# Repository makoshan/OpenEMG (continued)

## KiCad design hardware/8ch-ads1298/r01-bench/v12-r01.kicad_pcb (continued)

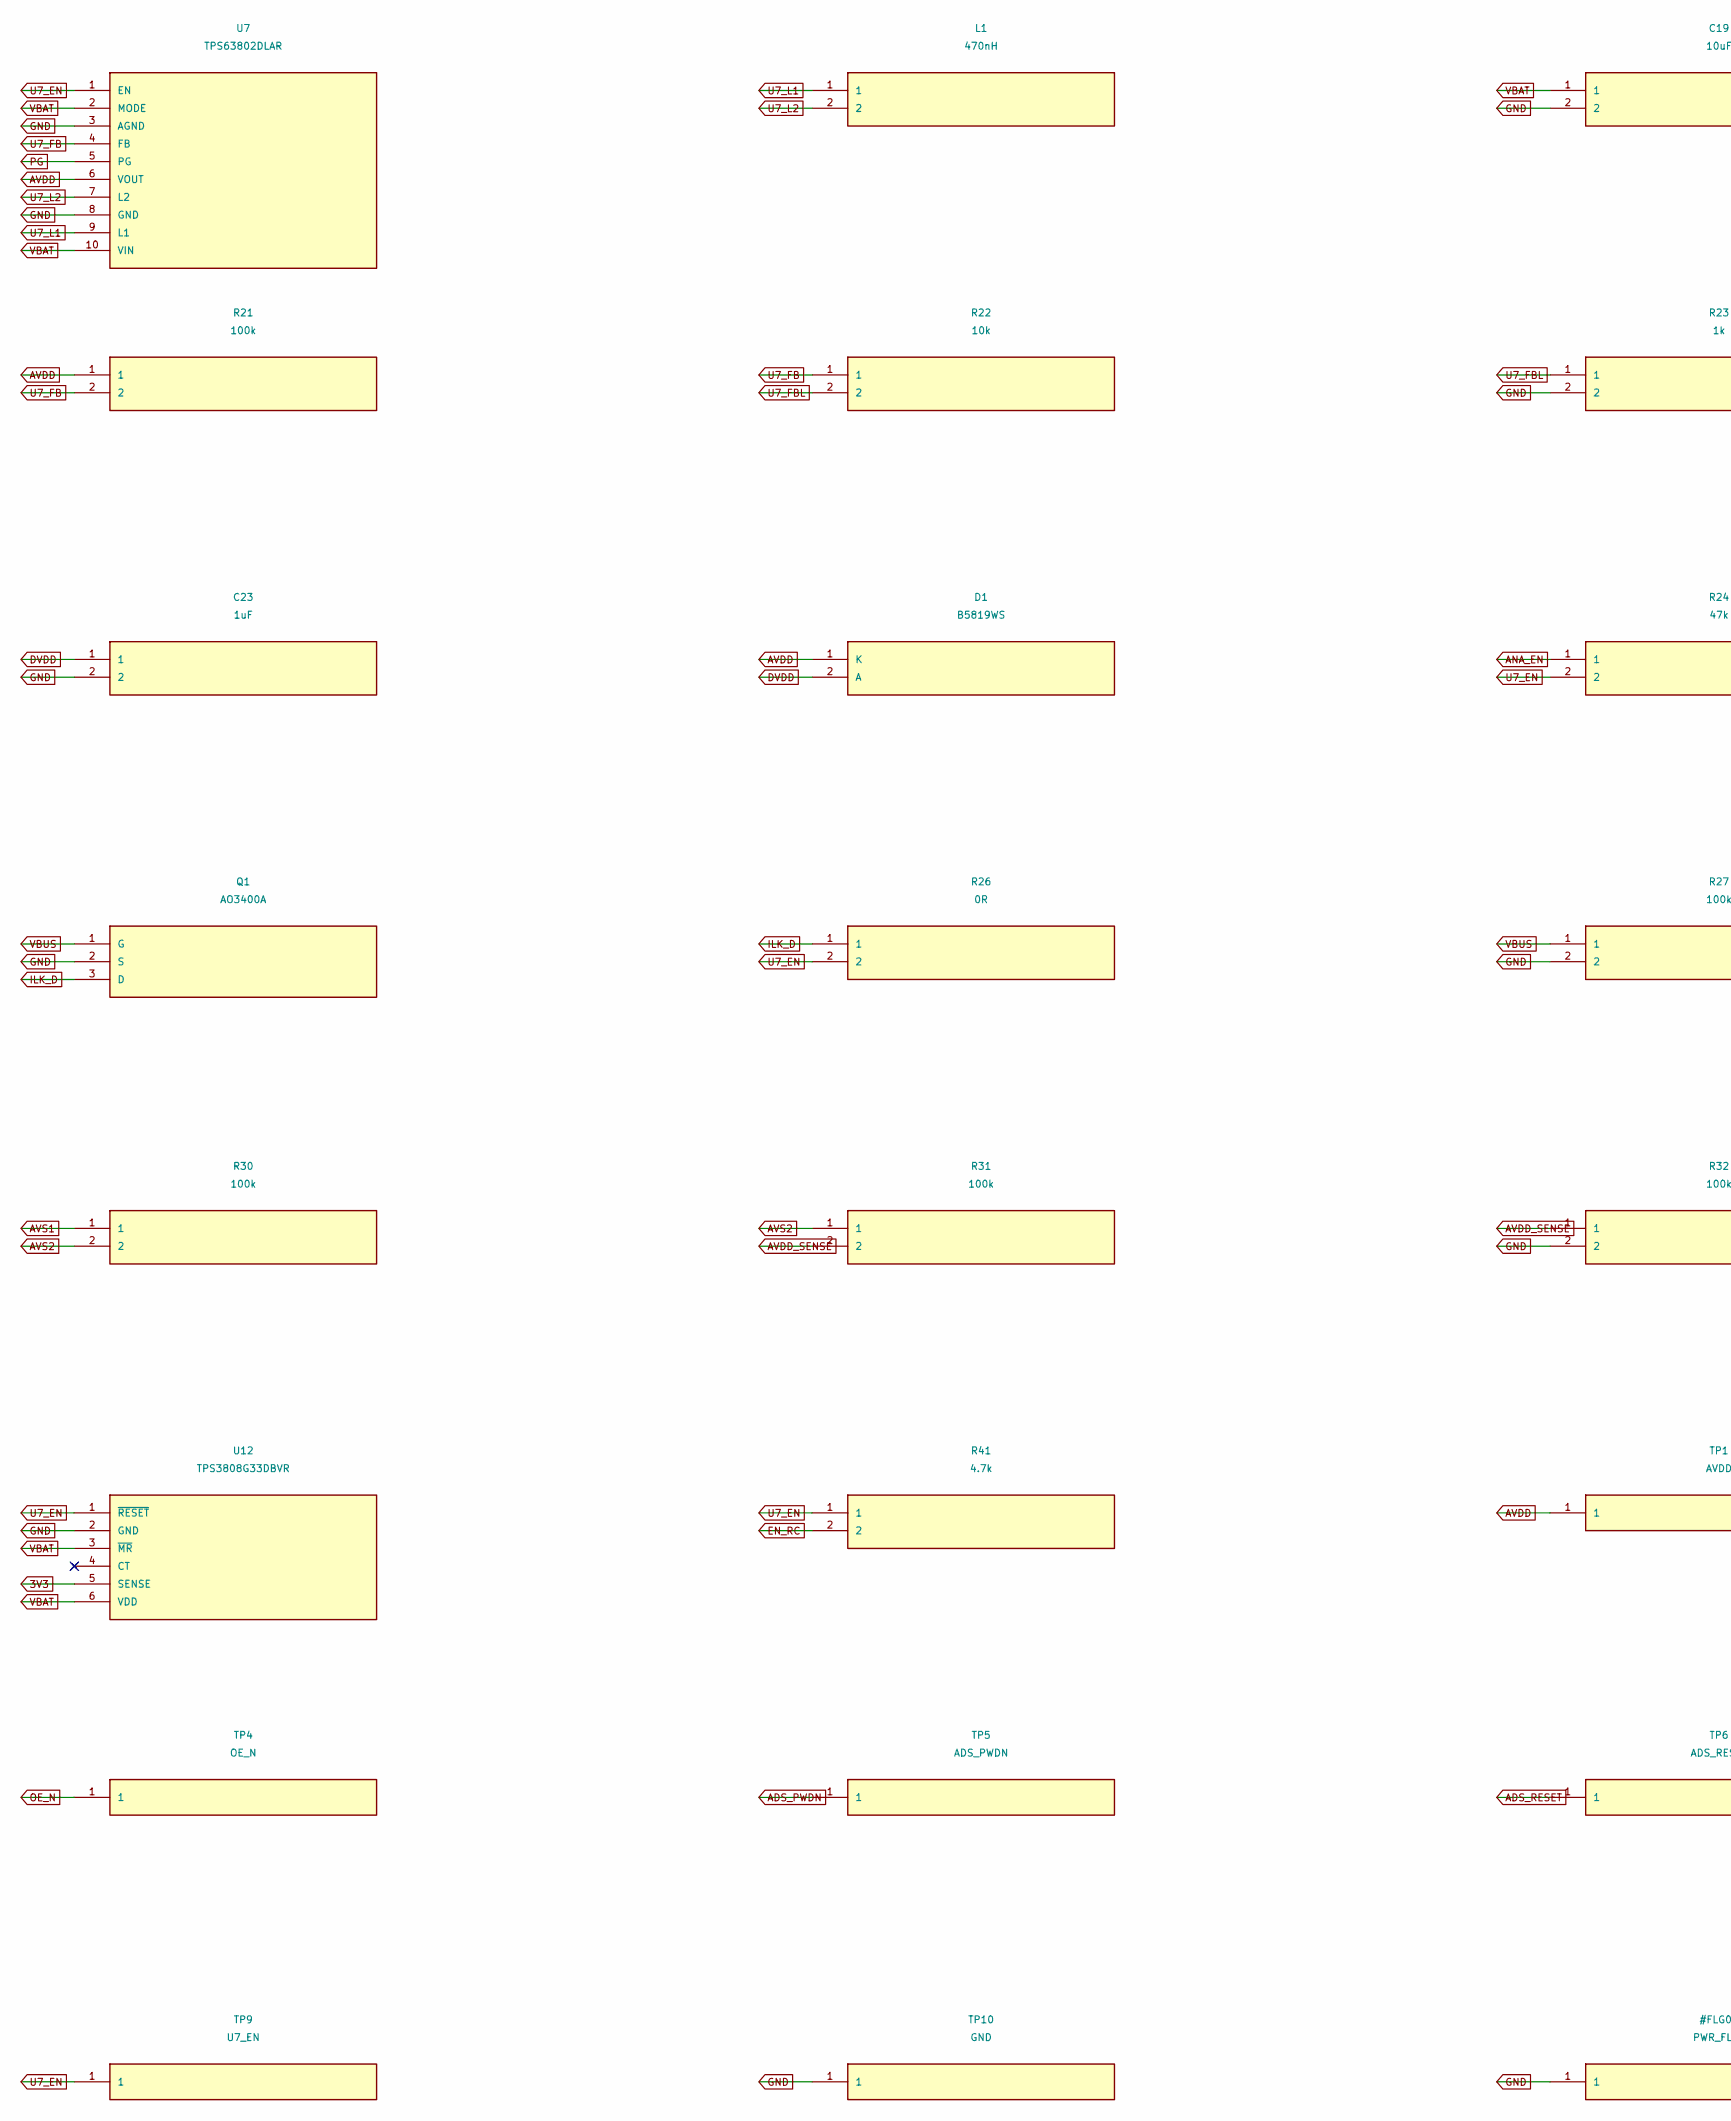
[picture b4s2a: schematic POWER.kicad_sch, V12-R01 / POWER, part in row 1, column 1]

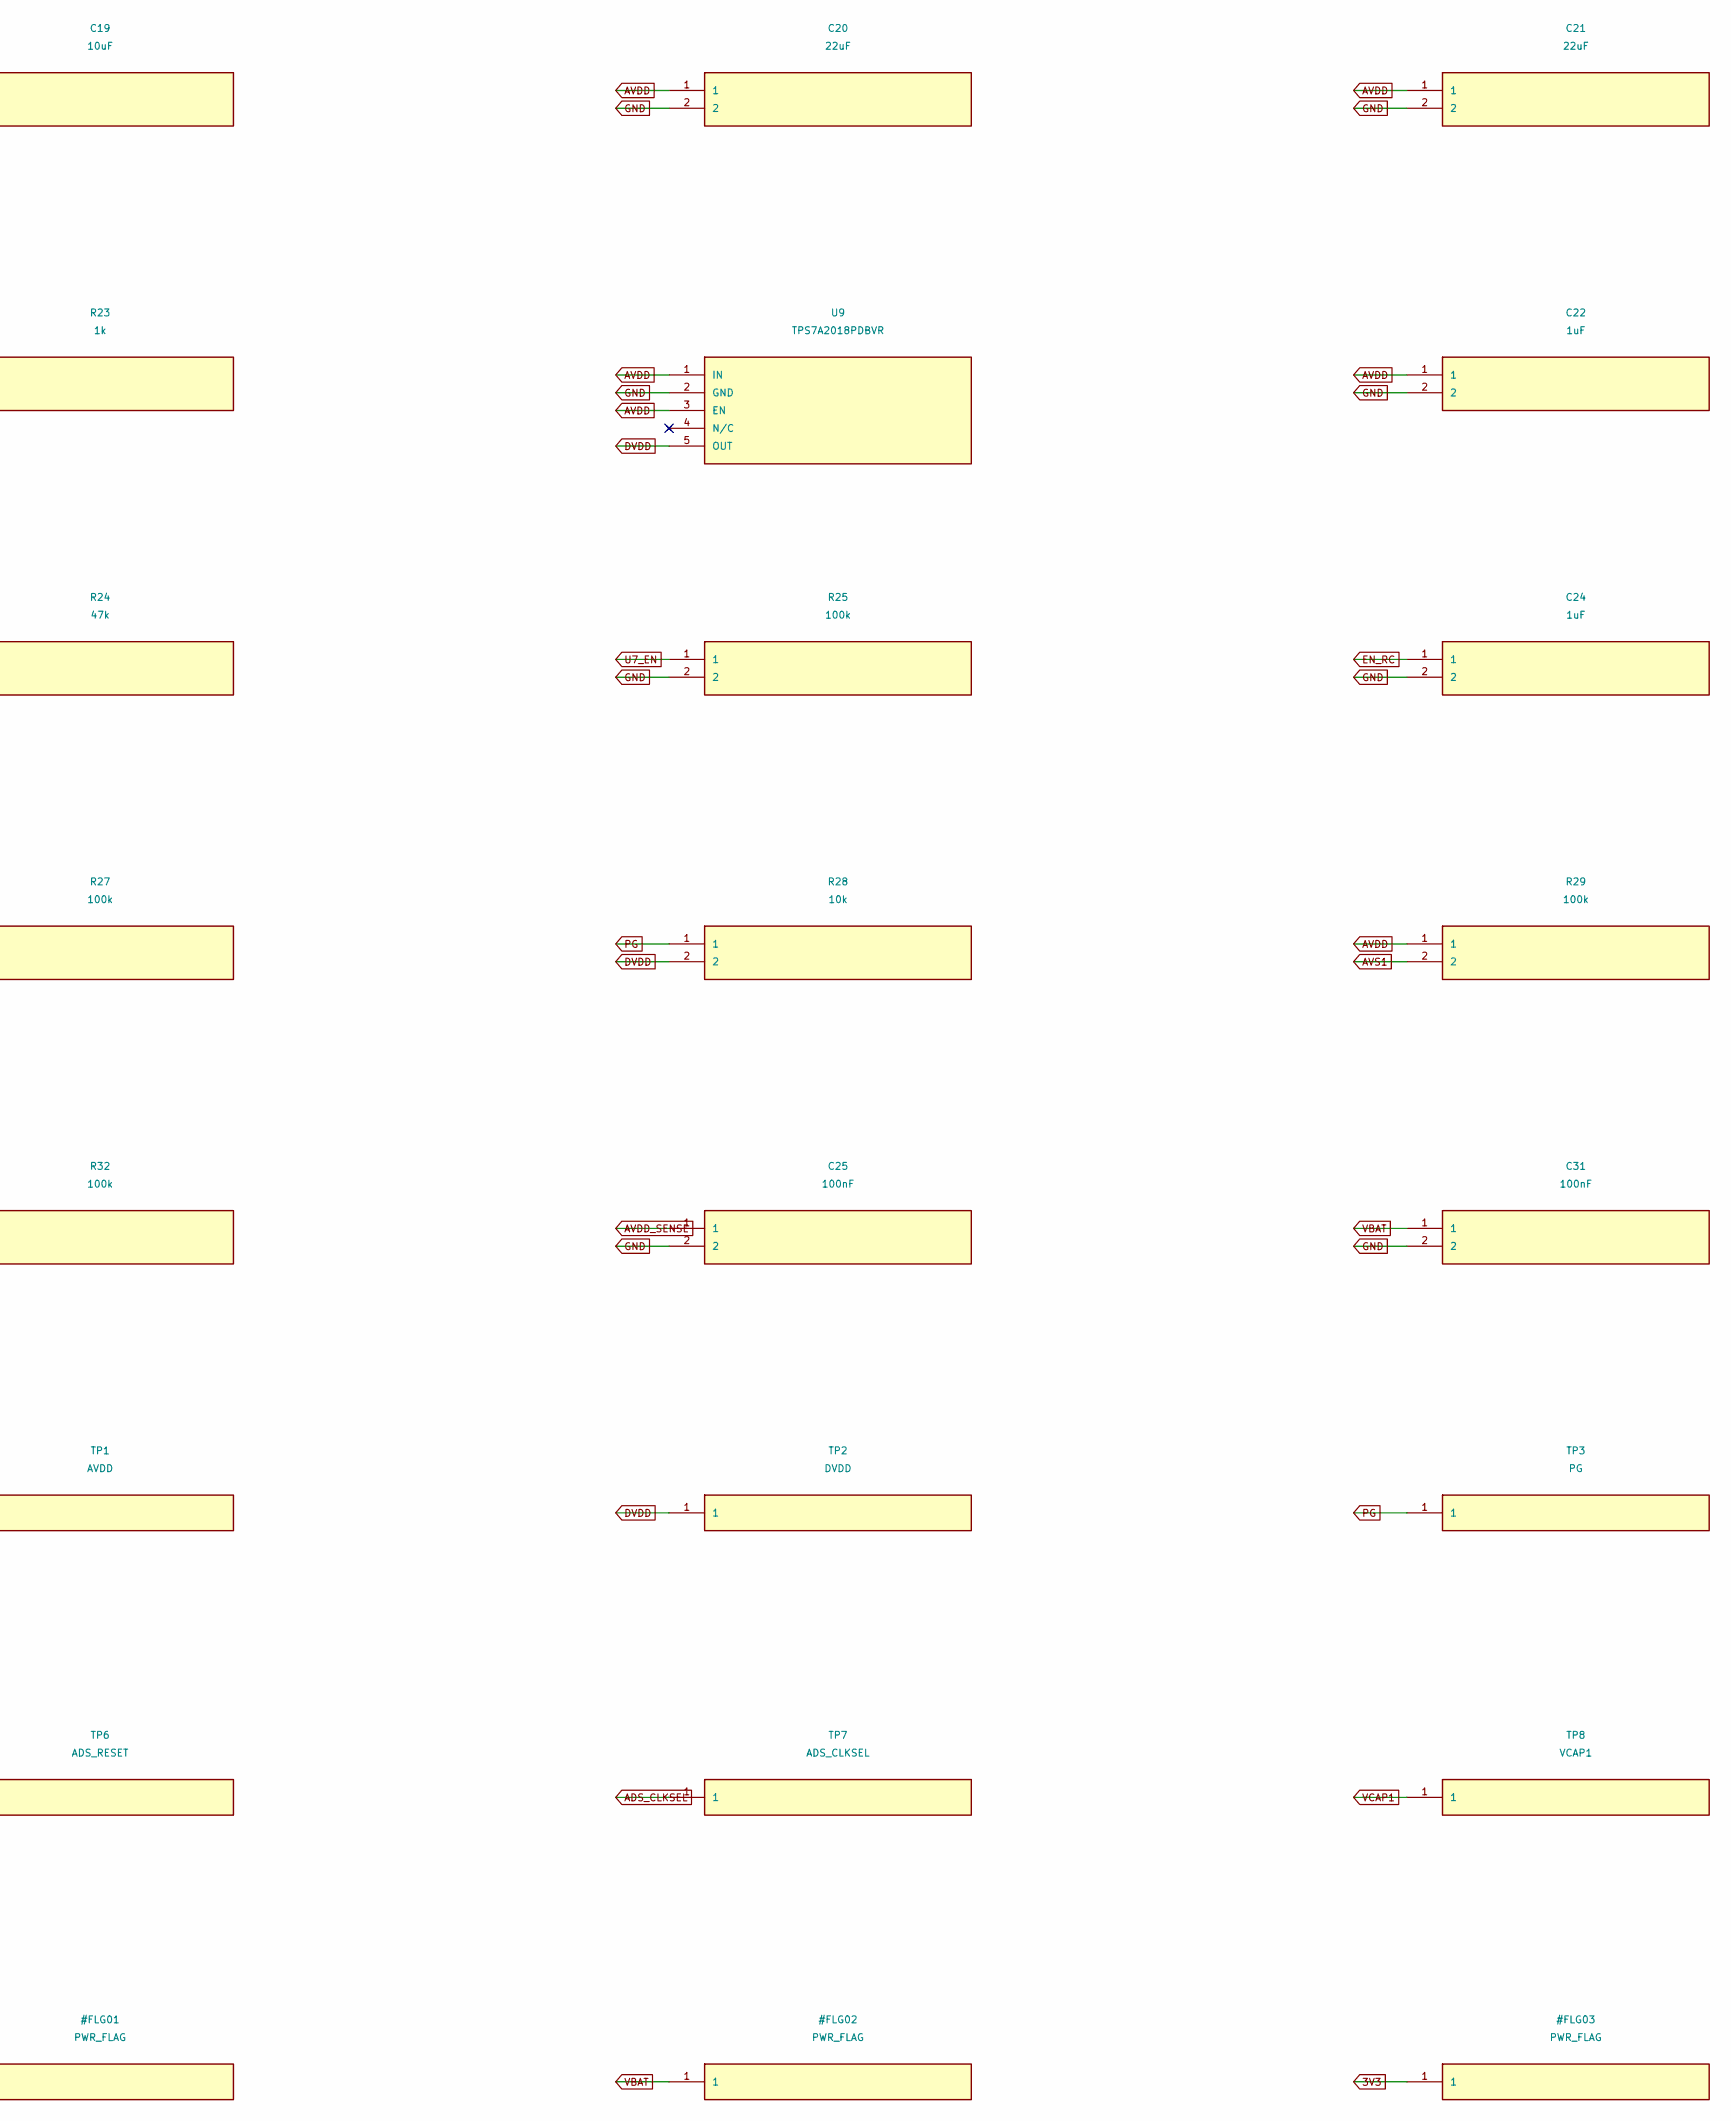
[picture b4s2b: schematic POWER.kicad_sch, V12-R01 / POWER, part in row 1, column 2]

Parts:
C19: 10uF; C_0603_1608Metric
C20, C21: 22uF; C_0805_2012Metric
C22, C23, C24: 1uF; C_0402_1005Metric
C25, C31: 100nF; C_0402_1005Metric
D1: B5819WS; D_SOD-323
L1: 470nH; FTC201610S
Q1: AO3400A; SOT-23
R21, R25, R27, R29, R30, R31, R32: 100k; R_0402_1005Metric
R22, R28: 10k; R_0402_1005Metric
R23: 1k; R_0402_1005Metric
R24: 47k; R_0402_1005Metric
R26: 0R; R_0402_1005Metric
R41: 4.7k; R_0402_1005Metric
TP1: AVDD; TestPoint_Pad_D1.0mm
TP2: DVDD; TestPoint_Pad_D1.0mm
TP3: PG; TestPoint_Pad_D1.0mm
TP4: OE_N; TestPoint_Pad_D1.0mm
TP5: ADS_PWDN; TestPoint_Pad_D1.0mm
TP6: ADS_RESET; TestPoint_Pad_D1.0mm
TP7: ADS_CLKSEL; TestPoint_Pad_D1.0mm
TP8: VCAP1; TestPoint_Pad_D1.0mm
TP9: U7_EN; TestPoint_Pad_D1.0mm
TP10: GND; TestPoint_Pad_D1.0mm
U7: TPS63802DLAR; TI_DLA0010A
U9: TPS7A2018PDBVR; SOT-23-5
U12: TPS3808G33DBVR; SOT-23-6

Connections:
3V3: U12.5 (SENSE); also elsewhere on the board
ADS_CLKSEL: TP7.1; also elsewhere on the board
ADS_PWDN: TP5.1; also elsewhere on the board
ADS_RESET: TP6.1; also elsewhere on the board
ANA_EN: R24.1; also elsewhere on the board
AVDD: C20.1, C21.1, C22.1, D1.1 (K), R21.1, R29.1, TP1.1, U7.6 (VOUT), U9.1 (IN), U9.3 (EN); also elsewhere on the board
AVDD_SENSE: C25.1, R31.2, R32.1; also elsewhere on the board
AVS1: R29.2, R30.1
AVS2: R30.2, R31.1
DVDD: C23.1, D1.2 (A), R28.2, TP2.1, U9.5 (OUT); also elsewhere on the board
EN_RC: C24.1, R41.2
GND: C19.2, C20.2, C21.2, C22.2, C23.2, C24.2, C25.2, C31.2, Q1.2 (S), R23.2, R25.2, R27.2, R32.2, TP10.1, U7.3 (AGND), U7.8 (GND), U9.2 (GND), U12.2 (GND); also elsewhere on the board
ILK_D: Q1.3 (D), R26.1
OE_N: TP4.1; also elsewhere on the board
PG: R28.1, TP3.1, U7.5 (PG); also elsewhere on the board
U7_EN: R24.2, R25.1, R26.2, R41.1, TP9.1, U7.1 (EN), U12.1 (~RESET)
U7_FB: R21.2, R22.1, U7.4 (FB)
U7_FBL: R22.2, R23.1
U7_L1: L1.1, U7.9 (L1)
U7_L2: L1.2, U7.7 (L2)
VBAT: C19.1, C31.1, U7.2 (MODE), U7.10 (VIN), U12.3 (~MR), U12.6 (VDD); also elsewhere on the board
VBUS: Q1.1 (G), R27.1; also elsewhere on the board
VCAP1: TP8.1; also elsewhere on the board

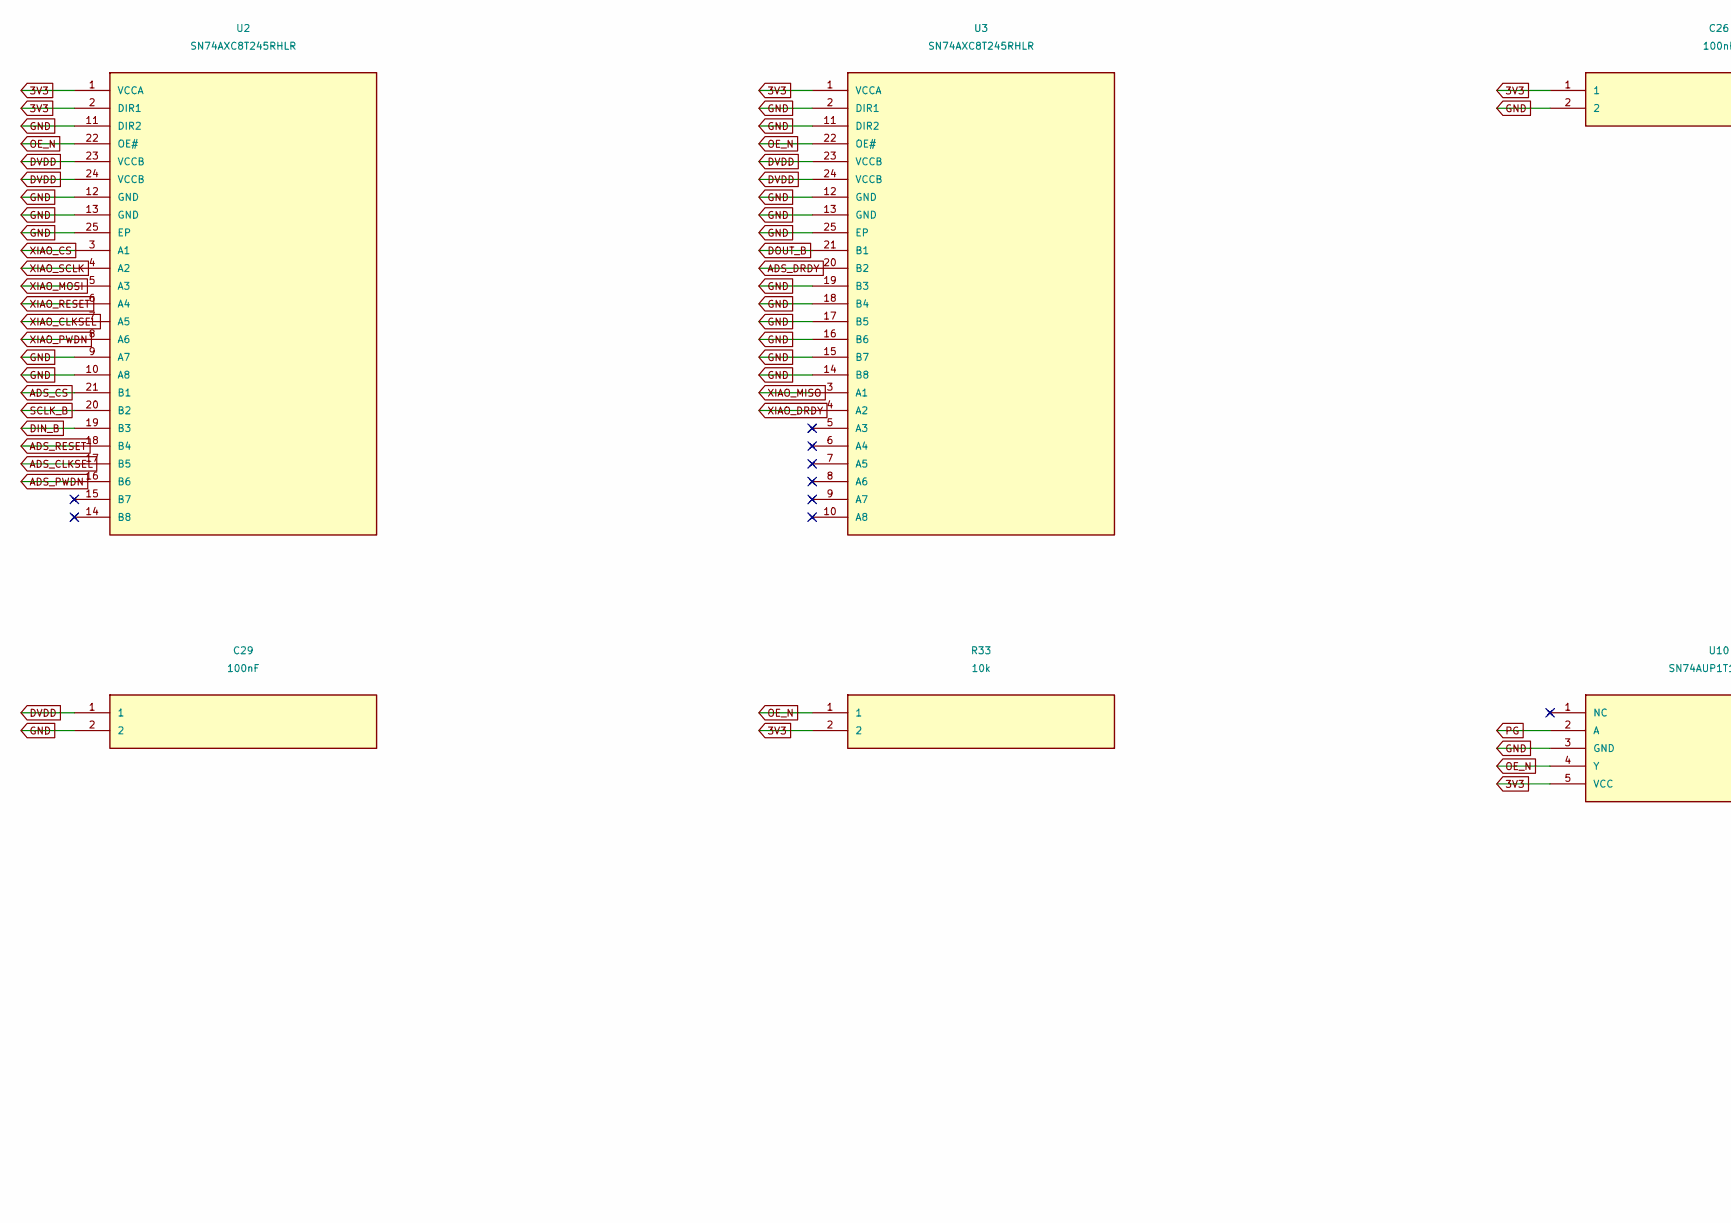
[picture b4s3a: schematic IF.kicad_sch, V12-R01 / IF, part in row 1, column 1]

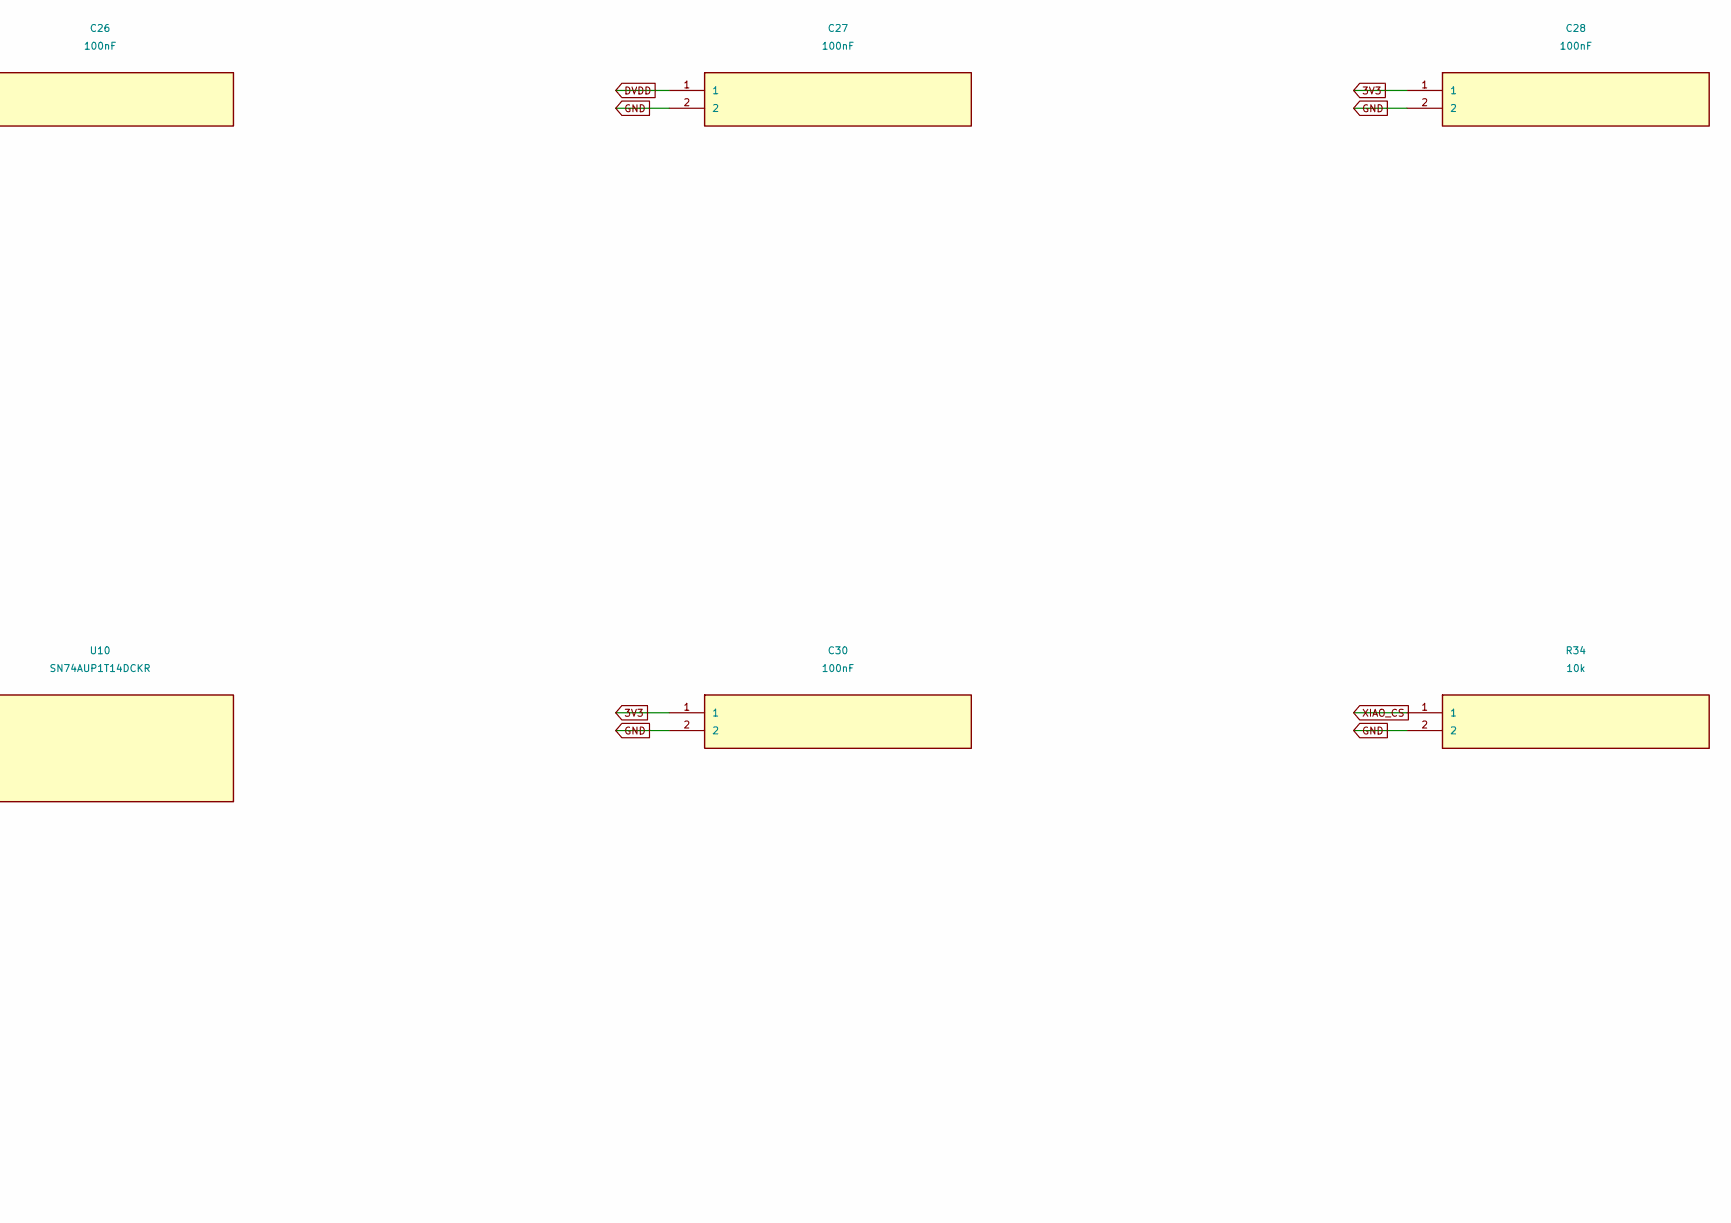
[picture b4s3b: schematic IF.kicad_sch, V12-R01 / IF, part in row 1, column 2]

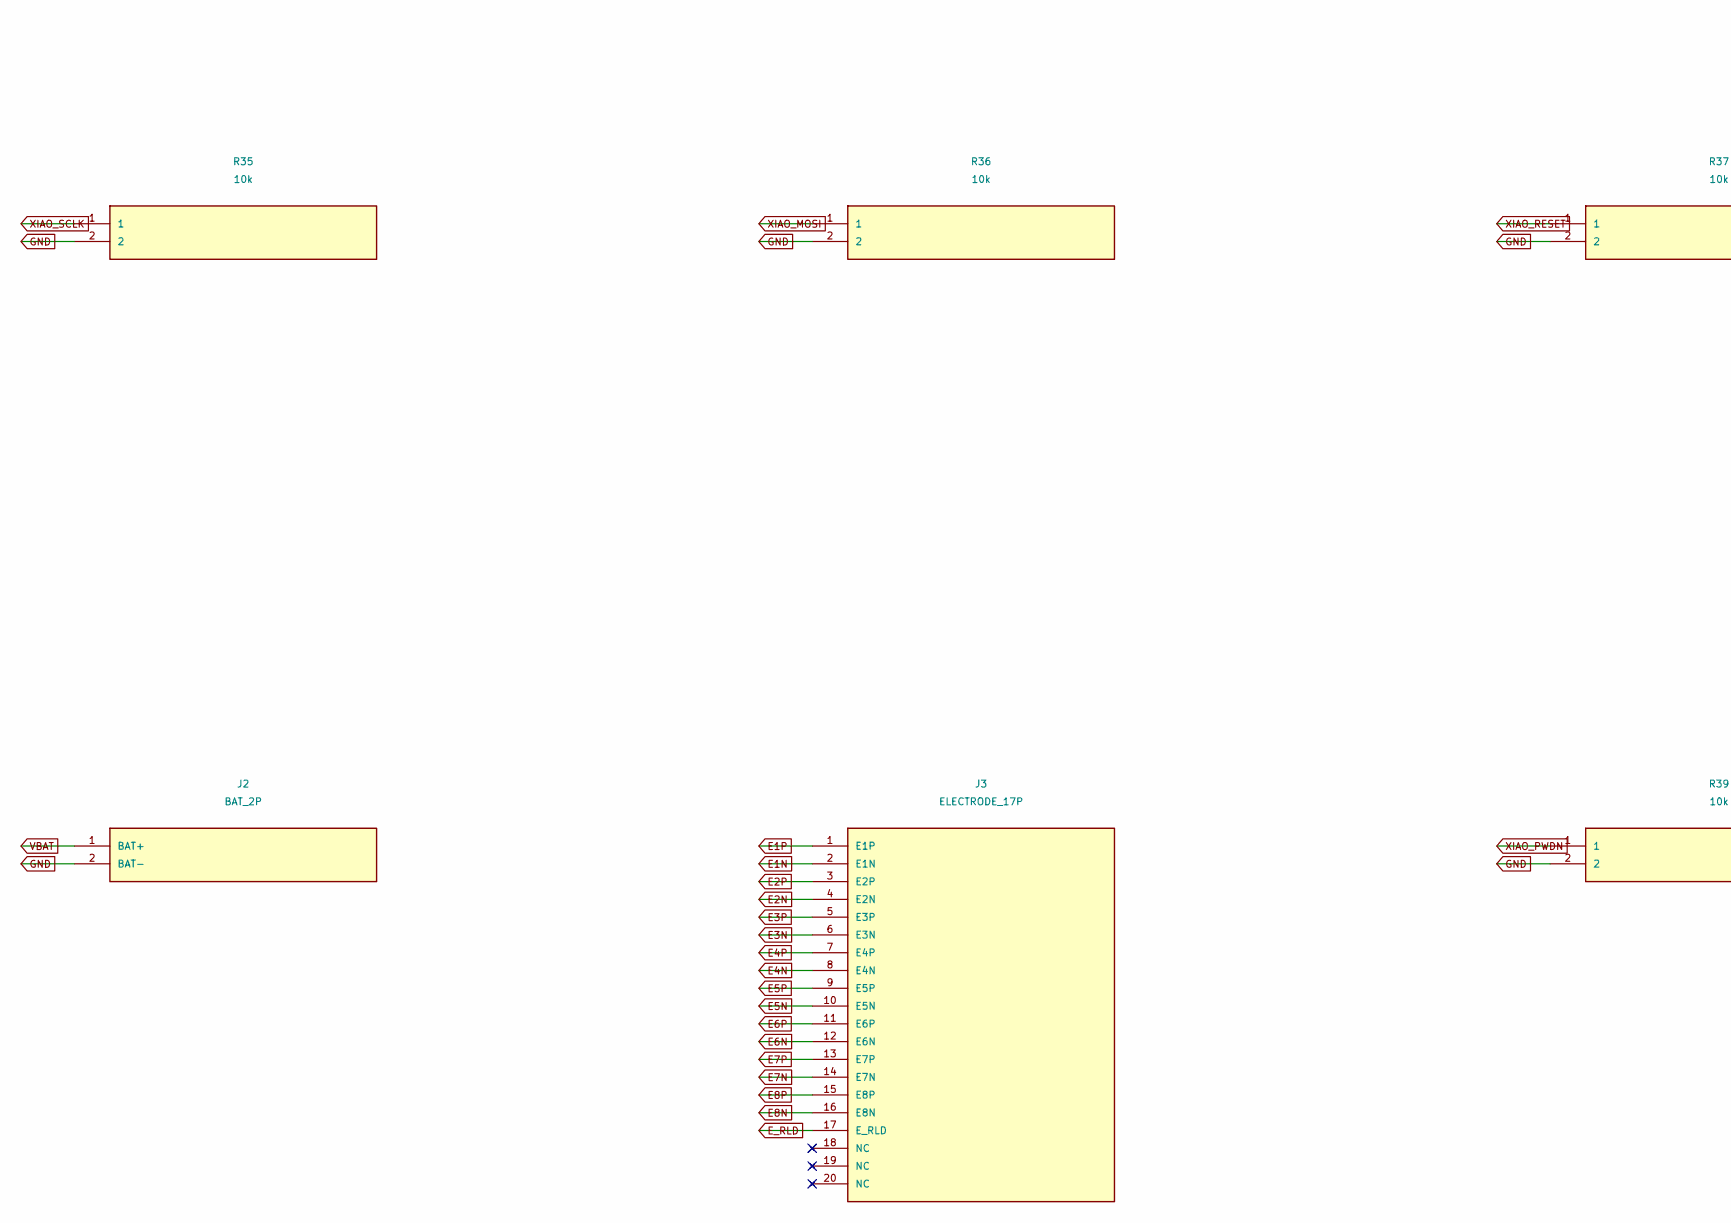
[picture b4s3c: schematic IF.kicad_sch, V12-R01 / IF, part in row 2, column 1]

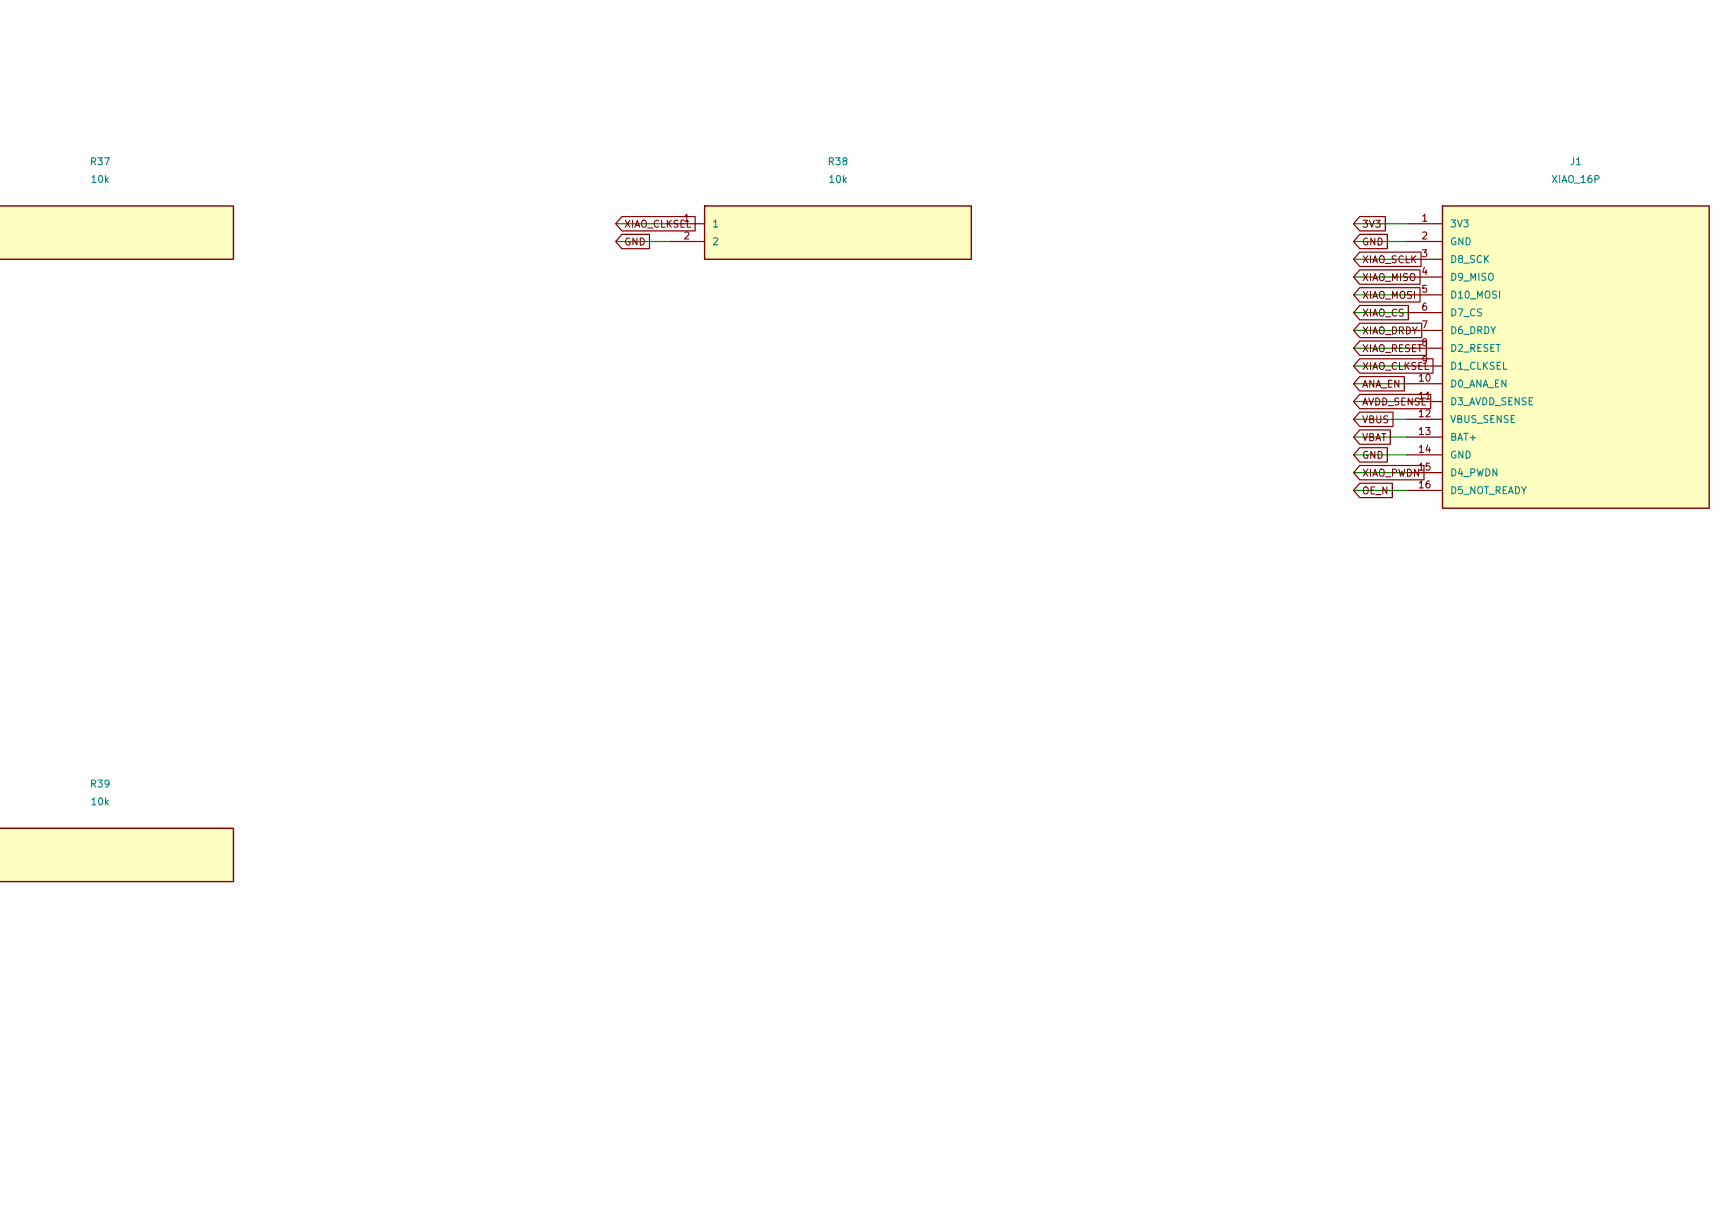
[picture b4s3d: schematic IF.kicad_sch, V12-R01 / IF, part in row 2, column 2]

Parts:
C26, C27, C28, C29, C30: 100nF; C_0402_1005Metric
J1: XIAO_16P; Samtec_TST-108-01-L-D
J2: BAT_2P; JST_PH_B2B-PH-K_1x02_P2.00mm_Vertical
J3: ELECTRODE_17P; Molex_Micro-Fit_3.0_43045-2012_2x10_P3.00mm_Vertical
R33, R34, R35, R36, R37, R38, R39: 10k; R_0402_1005Metric
U2, U3: SN74AXC8T245RHLR; TI_RHL0024A
U10: SN74AUP1T14DCKR; SOT-353_SC-70-5

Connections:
3V3: C26.1, C28.1, C30.1, J1.1 (3V3), R33.2, U2.1 (VCCA), U2.2 (DIR1), U3.1 (VCCA), U10.5 (VCC); also elsewhere on the board
ADS_CLKSEL: U2.17 (B5); also elsewhere on the board
ADS_CS: U2.21 (B1); also elsewhere on the board
ADS_DRDY: U3.20 (B2); also elsewhere on the board
ADS_PWDN: U2.16 (B6); also elsewhere on the board
ADS_RESET: U2.18 (B4); also elsewhere on the board
ANA_EN: J1.10 (D0_ANA_EN); also elsewhere on the board
AVDD_SENSE: J1.11 (D3_AVDD_SENSE); also elsewhere on the board
DIN_B: U2.19 (B3); also elsewhere on the board
DOUT_B: U3.21 (B1); also elsewhere on the board
DVDD: C27.1, C29.1, U2.23 (VCCB), U2.24 (VCCB), U3.23 (VCCB), U3.24 (VCCB); also elsewhere on the board
E1N: J3.2 (E1N); also elsewhere on the board
E1P: J3.1 (E1P); also elsewhere on the board
E2N: J3.4 (E2N); also elsewhere on the board
E2P: J3.3 (E2P); also elsewhere on the board
E3N: J3.6 (E3N); also elsewhere on the board
E3P: J3.5 (E3P); also elsewhere on the board
E4N: J3.8 (E4N); also elsewhere on the board
E4P: J3.7 (E4P); also elsewhere on the board
E5N: J3.10 (E5N); also elsewhere on the board
E5P: J3.9 (E5P); also elsewhere on the board
E6N: J3.12 (E6N); also elsewhere on the board
E6P: J3.11 (E6P); also elsewhere on the board
E7N: J3.14 (E7N); also elsewhere on the board
E7P: J3.13 (E7P); also elsewhere on the board
E8N: J3.16 (E8N); also elsewhere on the board
E8P: J3.15 (E8P); also elsewhere on the board
E_RLD: J3.17 (E_RLD); also elsewhere on the board
GND: C26.2, C27.2, C28.2, C29.2, C30.2, J1.2 (GND), J1.14 (GND), J2.2 (BAT-), R34.2, R35.2, R36.2, R37.2, R38.2, R39.2, U2.9 (A7), U2.10 (A8), U2.11 (DIR2), U2.12 (GND), U2.13 (GND), U2.25 (EP), U3.2 (DIR1), U3.11 (DIR2), U3.12 (GND), U3.13 (GND), U3.14 (B8), U3.15 (B7), U3.16 (B6), U3.17 (B5), U3.18 (B4), U3.19 (B3), U3.25 (EP), U10.3 (GND); also elsewhere on the board
OE_N: J1.16 (D5_NOT_READY), R33.1, U2.22 (OE#), U3.22 (OE#), U10.4 (Y); also elsewhere on the board
PG: U10.2 (A); also elsewhere on the board
SCLK_B: U2.20 (B2); also elsewhere on the board
VBAT: J1.13 (BAT+), J2.1 (BAT+); also elsewhere on the board
VBUS: J1.12 (VBUS_SENSE); also elsewhere on the board
XIAO_CLKSEL: J1.9 (D1_CLKSEL), R38.1, U2.7 (A5)
XIAO_CS: J1.6 (D7_CS), R34.1, U2.3 (A1)
XIAO_DRDY: J1.7 (D6_DRDY), U3.4 (A2)
XIAO_MISO: J1.4 (D9_MISO), U3.3 (A1)
XIAO_MOSI: J1.5 (D10_MOSI), R36.1, U2.5 (A3)
XIAO_PWDN: J1.15 (D4_PWDN), R39.1, U2.8 (A6)
XIAO_RESET: J1.8 (D2_RESET), R37.1, U2.6 (A4)
XIAO_SCLK: J1.3 (D8_SCK), R35.1, U2.4 (A2)

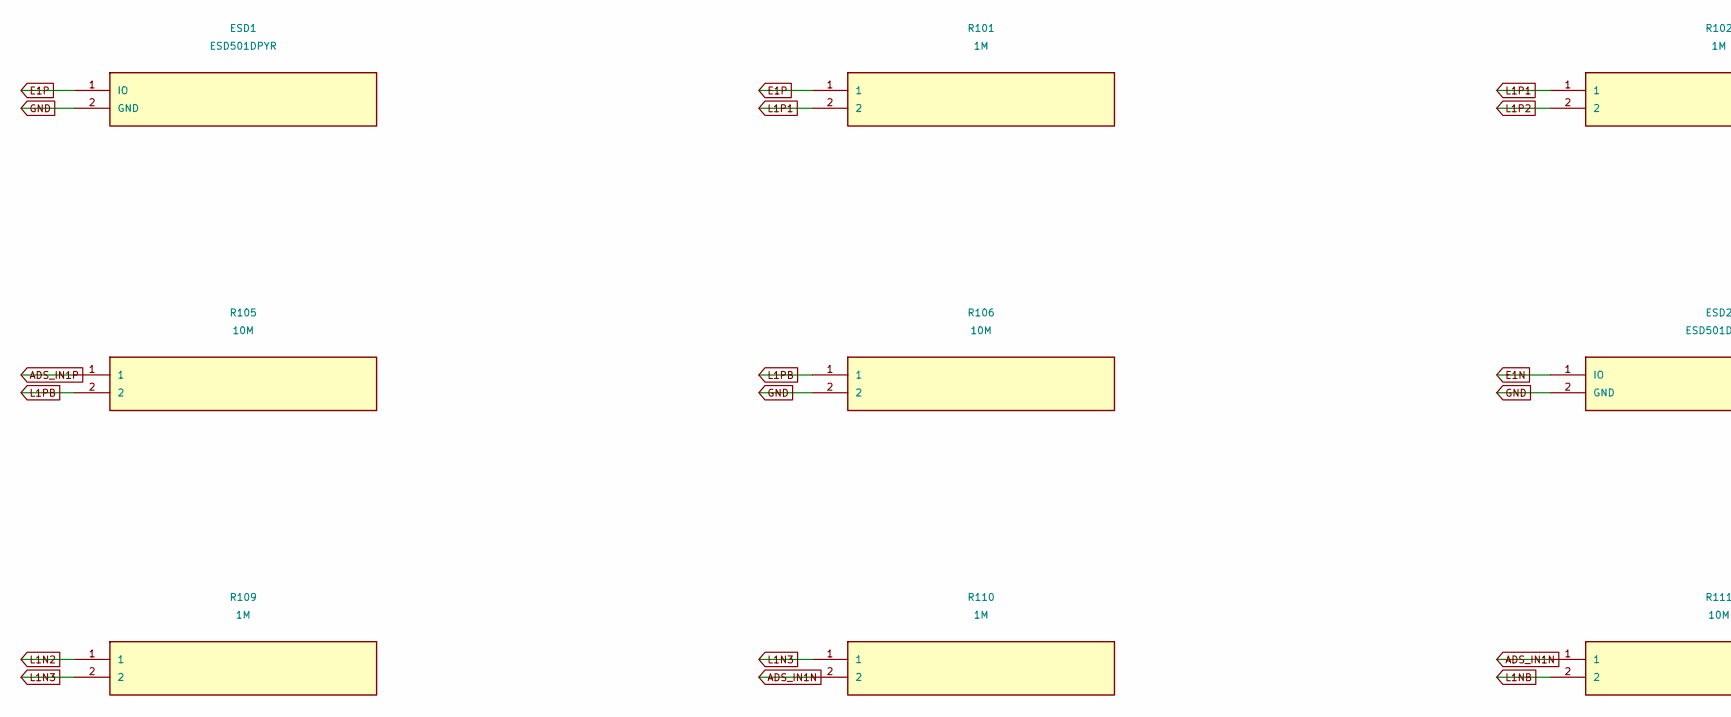
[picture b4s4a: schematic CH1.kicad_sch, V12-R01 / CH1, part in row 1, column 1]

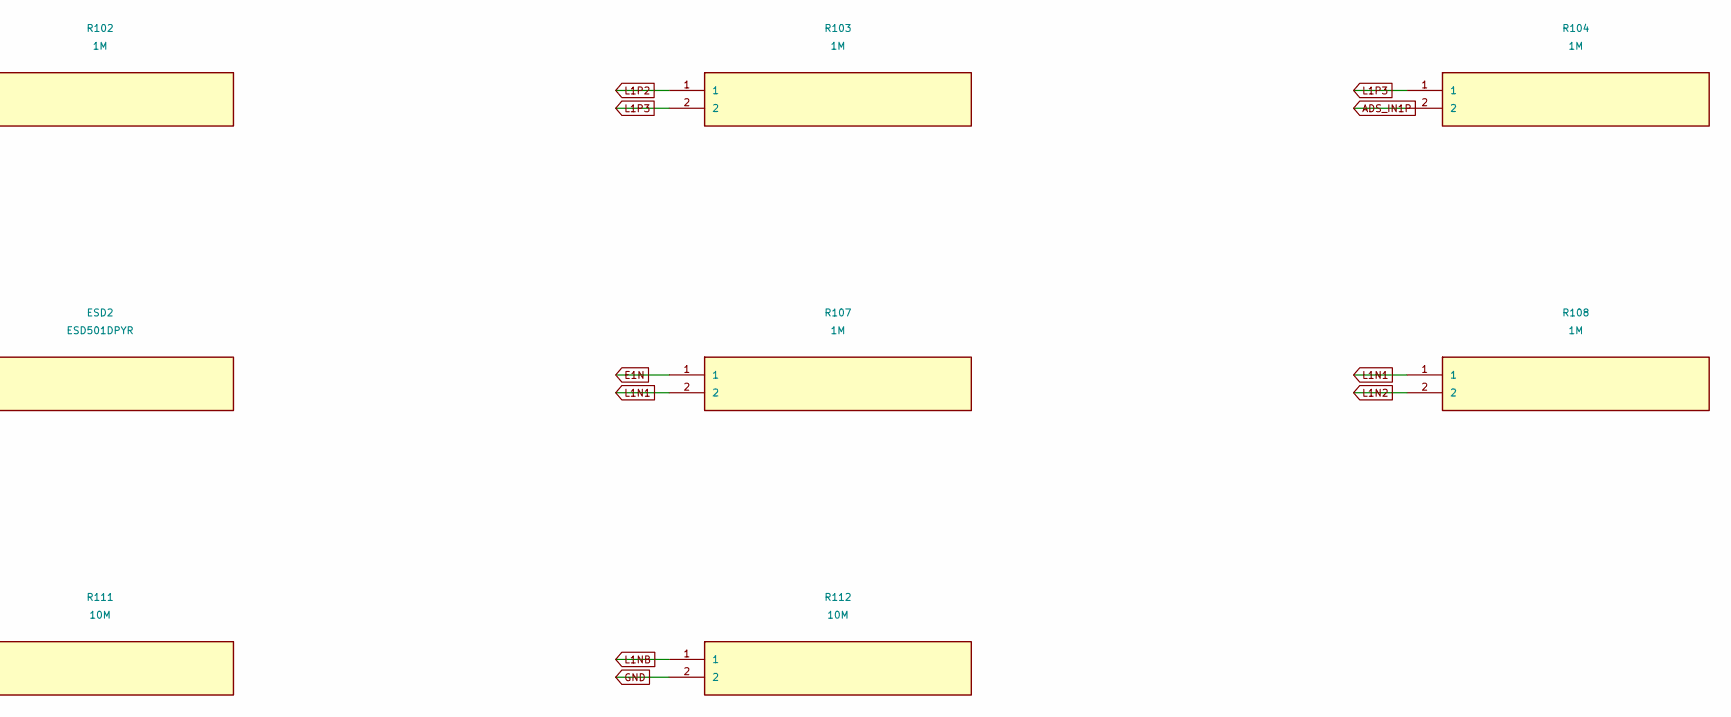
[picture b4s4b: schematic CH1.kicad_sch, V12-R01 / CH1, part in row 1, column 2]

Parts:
ESD1, ESD2: ESD501DPYR; Texas_DPY0002A_0.6x1mm_P0.65mm
R101, R102, R103, R104, R107, R108, R109, R110: 1M; R_0402_1005Metric
R105, R106, R111, R112: 10M; R_0402_1005Metric

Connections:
ADS_IN1N: R110.2, R111.1; also elsewhere on the board
ADS_IN1P: R104.2, R105.1; also elsewhere on the board
E1N: ESD2.1 (IO), R107.1; also elsewhere on the board
E1P: ESD1.1 (IO), R101.1; also elsewhere on the board
GND: ESD1.2 (GND), ESD2.2 (GND), R106.2, R112.2; also elsewhere on the board
L1N1: R107.2, R108.1
L1N2: R108.2, R109.1
L1N3: R109.2, R110.1
L1NB: R111.2, R112.1
L1P1: R101.2, R102.1
L1P2: R102.2, R103.1
L1P3: R103.2, R104.1
L1PB: R105.2, R106.1
